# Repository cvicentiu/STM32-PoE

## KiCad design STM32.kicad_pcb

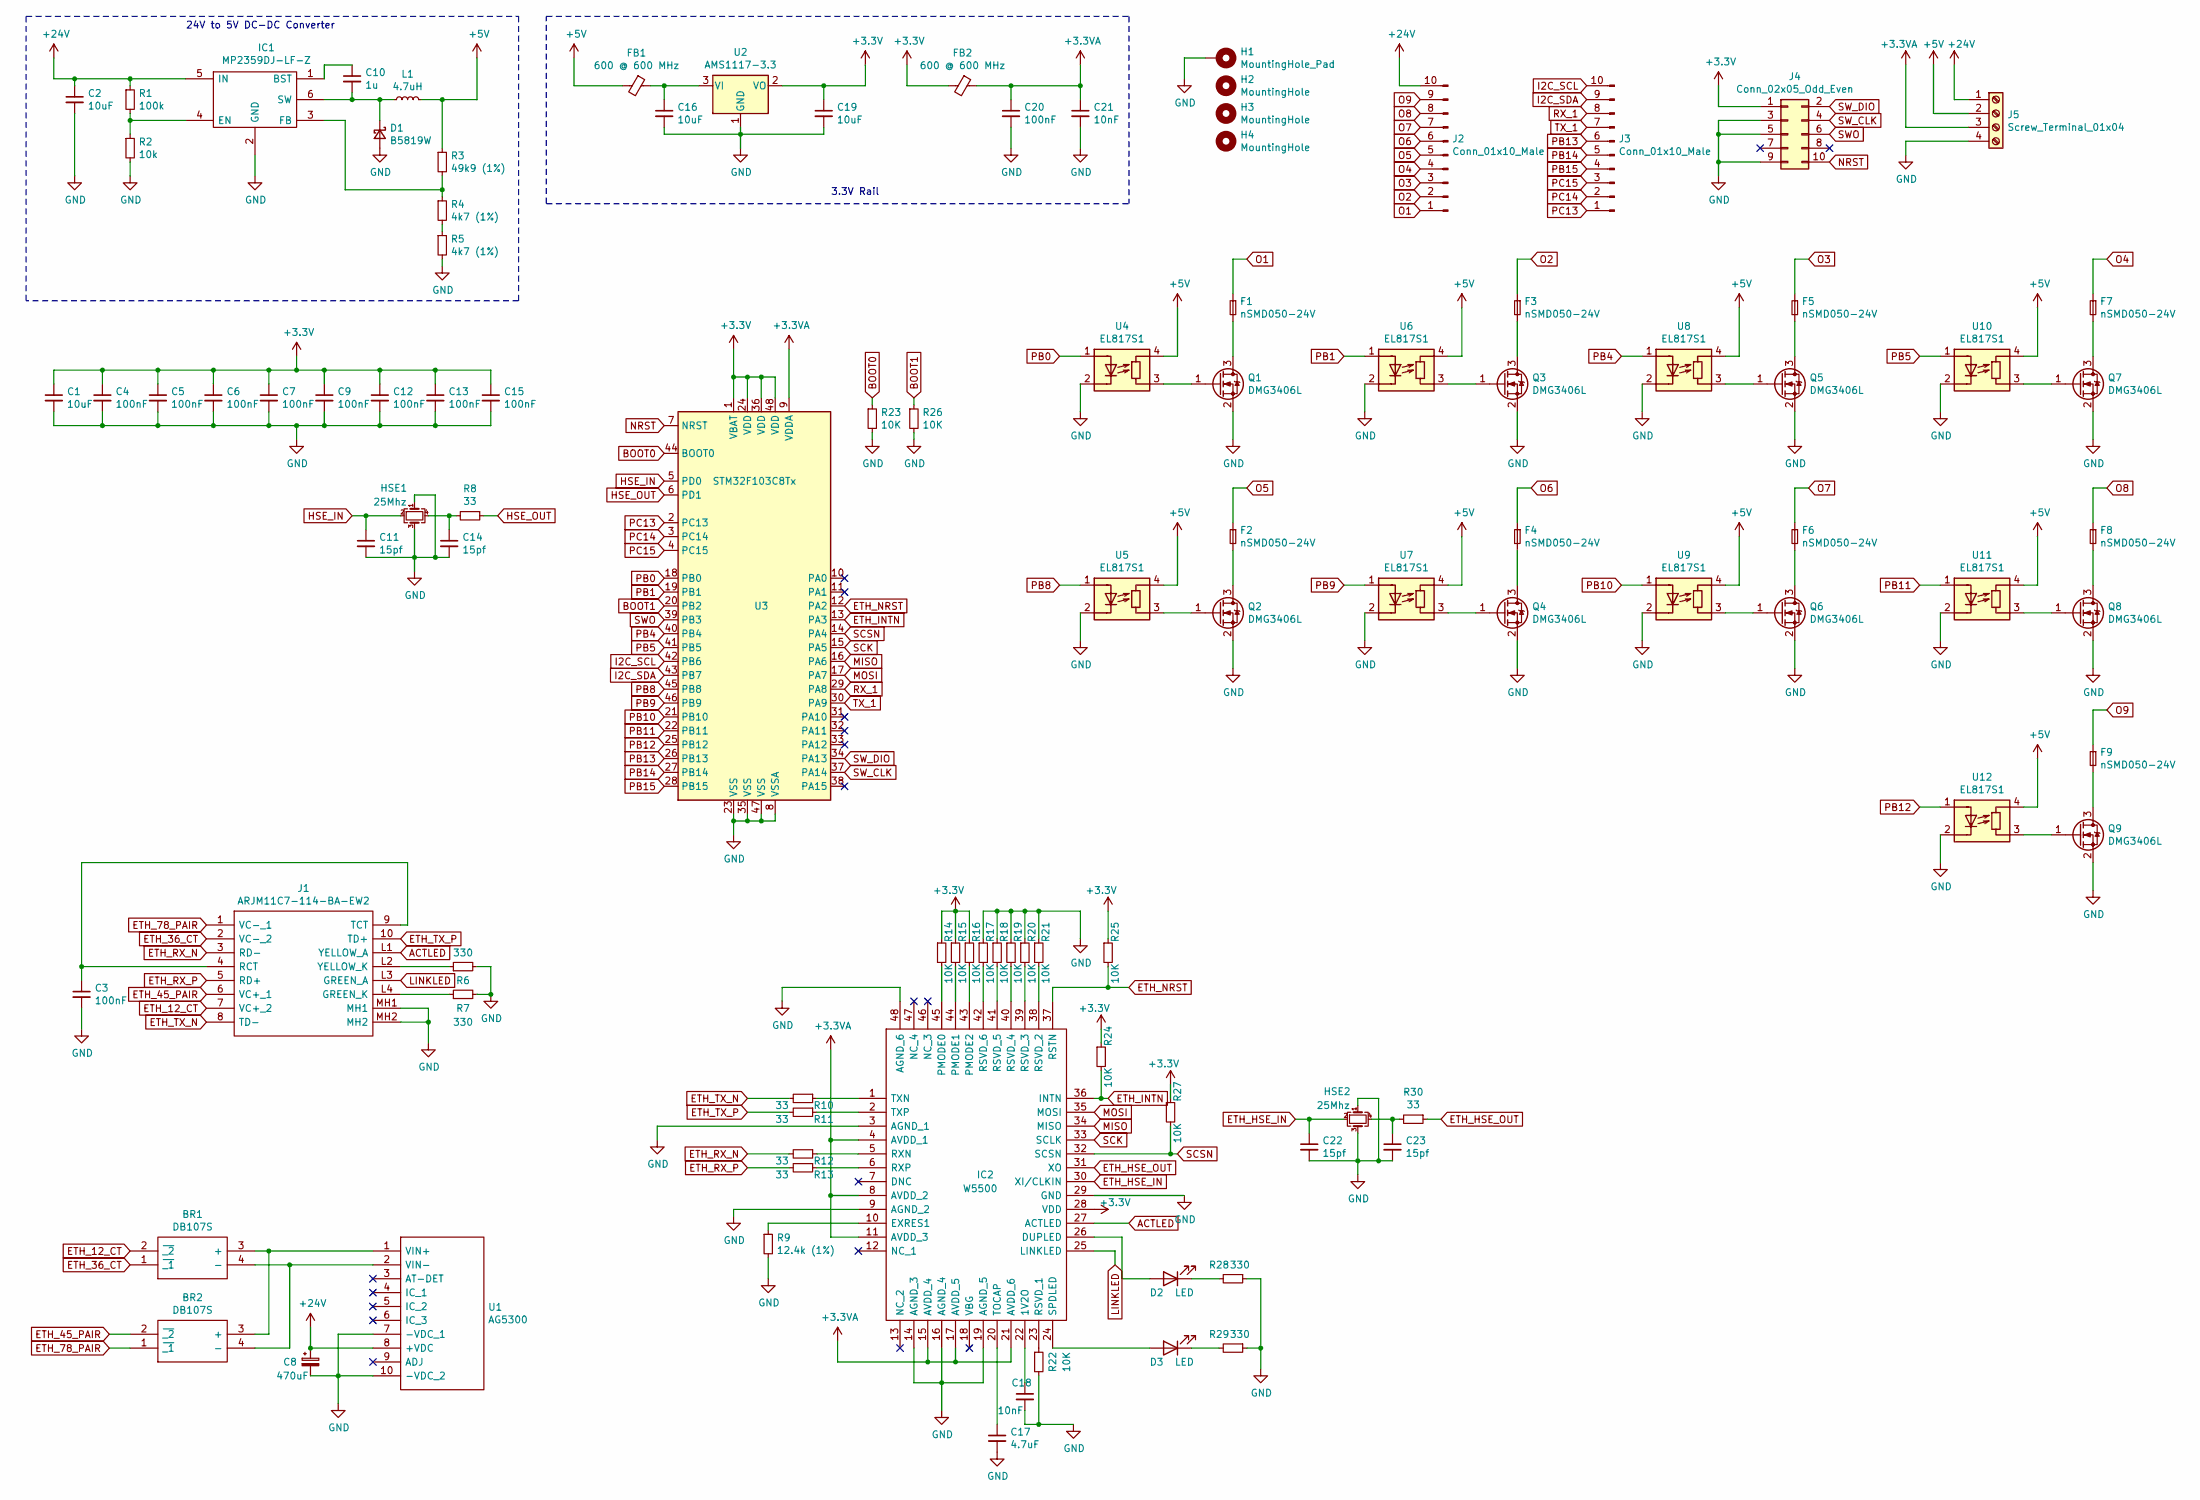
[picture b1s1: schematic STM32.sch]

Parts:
BR1, BR2: DB107S; SOP510P990X340-4N; Manufacturer_Part_Number DB107S; Mouser Part Number 583-DB107S
C1, C16, C19: 10uF; C_0402_1005Metric
C2: 10uF; C_0805_2012Metric
C3, C4, C5, C6, C7, C9, C12, C13, C15, C20: 100nF; C_0402_1005Metric
C8: 470uF; CP_Elec_10x10
C10: 1u; C_0805_2012Metric
C11, C14, C22, C23: 15pf; C_0402_1005Metric
C17: 4.7uF; C_0402_1005Metric
C18, C21: 10nF; C_0402_1005Metric
D1: B5819W; D_SOD-123
D2, D3: LED; LED_0805_2012Metric
F1, F2, F3, F4, F5, F6, F7, F8, F9: nSMD050-24V; Fuse_1206_3216Metric
FB1, FB2: 600 @ 600 MHz; L_0805_2012Metric
H1: MountingHole_Pad; MountingHole_3.2mm_M3_Pad_Via
H2, H3, H4: MountingHole; MountingHole_3.2mm_M3_Pad_Via
HSE1, HSE2: 25Mhz; Crystal_SMD_3225-4Pin_3.2x2.5mm
IC1: MP2359DJ-LF-Z; MP2359; Manufacturer_Part_Number MP2359DJ-LF-Z; Mouser Part Number 946-MP2359DJLFZ
IC2: W5500; QFP50P900X900X160-48N; Manufacturer_Part_Number W5500; Mouser Part Number 950-W5500
J1: ARJM11C7-114-BA-EW2; ARJM11C7114BAEW2; Manufacturer_Part_Number ARJM11C7-114-BA-EW2; Mouser Part Number 815-RJM11C7114BAEW2
J2, J3: Conn_01x10_Male; PinHeader_1x10_P2.54mm_Vertical
J4: Conn_02x05_Odd_Even; IDC-Header_2x05_P2.54mm_Vertical
J5: Screw_Terminal_01x04; TerminalBlock_Phoenix_MKDS-1,5-4_1x04_P5.00mm_Horizontal
L1: 4.7uH; L_1812_4532Metric
Q1, Q2, Q3, Q4, Q5, Q6, Q7, Q8, Q9: DMG3406L; SOT-23
R1: 100k; R_0805_2012Metric
R2: 10k; R_0805_2012Metric
R3: 49k9 (1%); R_0402_1005Metric
R4, R5: 4k7 (1%); R_0402_1005Metric
R6, R7, R28, R29: 330; R_0402_1005Metric
R8, R10, R11, R12, R13, R30: 33; R_0402_1005Metric
R9: 12.4k (1%); R_0402_1005Metric
R14, R15, R16, R17, R18, R19, R20, R21, R22, R23, R24, R25, R26, R27: 10K; R_0402_1005Metric
U1: AG5300; Manufacturer_Part_Number AG5300; Mouser Part Number 480-AG5300
U2: AMS1117-3.3; SOT-223-3_TabPin2
U3: STM32F103C8Tx; LQFP-48_7x7mm_P0.5mm
U4, U5, U6, U7, U8, U9, U10, U11, U12: EL817S1; SOP254P1030X390-4N

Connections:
+3.3VA: C20.1, C21.1, FB2.1, IC2.4 (AVDD_1), IC2.8 (AVDD_2), IC2.11 (AVDD_3), IC2.15 (AVDD_4), IC2.17 (AVDD_5), IC2.21 (AVDD_6), J5.3, U3.9 (VDDA)
+3V3: C1.1, C4.1, C5.1, C6.1, C7.1, C9.1, C12.1, C13.1, C15.1, C19.1, FB2.2, IC2.28 (VDD), J4.1, R14.1, R15.1, R16.1, R24.1, R25.1, R27.1, U2.2 (VO), U3.1 (VBAT), U3.24 (VDD), U3.36 (VDD), U3.48 (VDD)
+5V: FB1.2, J5.2, L1.2, R3.1, U4.4 (R), U5.4 (R), U6.4 (R), U7.4 (R), U8.4 (R), U9.4 (R), U10.4 (R), U11.4 (R), U12.4 (R)
+24V: C2.1, C8.1, IC1.5 (IN), J2.10, J5.1, R1.1, U1.8 (+VDC)
ACTLED: IC2.27 (ACTLED), J1.L1 (YELLOW_A)
BOOT0: R23.1, U3.44 (BOOT0)
BOOT1: R26.1, U3.20 (PB2)
ETH_12_CT: BR1.2 (~_2), J1.7 (VC+_2)
ETH_36_CT: BR1.1 (~_1), J1.2 (VC-_2)
ETH_45_PAIR: BR2.2 (~_2), J1.6 (VC+_1)
ETH_78_PAIR: BR2.1 (~_1), J1.1 (VC-_1)
ETH_HSE_IN: C22.1, HSE2.2, IC2.30 (XI/CLKIN)
ETH_HSE_OUT: IC2.31 (XO), R30.1
ETH_INTN: IC2.36 (INTN), R24.2, U3.13 (PA3)
ETH_NRST: IC2.37 (RSTN), R25.2, U3.12 (PA2)
ETH_RX_N: J1.3 (RD-), R12.2
ETH_RX_P: J1.5 (RD+), R13.2
ETH_TX_N: J1.8 (TD-), R10.2
ETH_TX_P: J1.10 (TD+), R11.2
GND: C1.2, C2.2, C3.2, C4.2, C5.2, C6.2, C7.2, C8.2, C9.2, C11.2, C12.2, C13.2, C14.2, C15.2, C16.2, C17.2, C18.2, C19.2, C20.2, C21.2, C22.2, C23.2, D1.2 (A), H1.1, HSE1.1, HSE1.3, HSE2.1, HSE2.3, IC1.2 (GND), IC2.3 (AGND_1), IC2.9 (AGND_2), IC2.14 (AGND_3), IC2.16 (AGND_4), IC2.19 (AGND_5), IC2.29 (GND), IC2.48 (AGND_6), J1.MH1, J1.MH2, J4.3, J4.5, J4.9, J5.4, Q1.2 (S), Q2.2 (S), Q3.2 (S), Q4.2 (S), Q5.2 (S), Q6.2 (S), Q7.2 (S), Q8.2 (S), Q9.2 (S), R2.2, R5.2, R6.2, R7.2, R9.2, R17.1, R18.1, R19.1, R20.1, R21.1, R22.2, R23.2, R26.2, R28.1, R29.1, U1.7 (-VDC_1), U1.10 (-VDC_2), U2.1 (GND), U3.8 (VSSA), U3.23 (VSS), U3.35 (VSS), U3.47 (VSS), U4.2 (K), U5.2 (K), U6.2 (K), U7.2 (K), U8.2 (K), U9.2 (K), U10.2 (K), U11.2 (K), U12.2 (K)
HSE_IN: C11.1, HSE1.2, U3.5 (PD0)
HSE_OUT: R8.1, U3.6 (PD1)
I2C_SCL: J3.10, U3.42 (PB6)
I2C_SDA: J3.9, U3.43 (PB7)
LINKLED: IC2.25 (LINKLED), J1.L3 (GREEN_A)
MISO: IC2.34 (MISO), U3.16 (PA6)
MOSI: IC2.35 (MOSI), U3.17 (PA7)
NRST: J4.10, U3.7 (NRST)
unnamed: BR1.3 (+), BR2.3 (+), U1.1 (VIN+)
unnamed: BR1.4 (-), BR2.4 (-), U1.2 (VIN-)
unnamed: C3.1, J1.4 (RCT), J1.9 (TCT)
unnamed: C10.1, IC1.1 (BST)
unnamed: C10.2, D1.1 (K), IC1.6 (SW), L1.1
unnamed: C14.1, HSE1.4, R8.2
unnamed: C16.1, FB1.1, U2.3 (VI)
unnamed: C17.1, IC2.20 (TOCAP)
unnamed: C18.1, IC2.22 (1V2O)
unnamed: C23.1, HSE2.4, R30.2
unnamed: D2.1 (K), R28.2
unnamed: D2.2 (A), IC2.26 (DUPLED)
unnamed: D3.1 (K), R29.2
unnamed: D3.2 (A), IC2.24 (SPDLED)
unnamed: F1.2, Q1.3 (D)
unnamed: F2.2, Q2.3 (D)
unnamed: F3.2, Q3.3 (D)
unnamed: F4.2, Q4.3 (D)
unnamed: F5.2, Q5.3 (D)
unnamed: F6.2, Q6.3 (D)
unnamed: F7.2, Q7.3 (D)
unnamed: F8.2, Q8.3 (D)
unnamed: F9.2, Q9.3 (D)
unnamed: IC1.3 (FB), R3.2, R4.1
unnamed: IC1.4 (EN), R1.2, R2.1
unnamed: IC2.1 (TXN), R10.1
unnamed: IC2.2 (TXP), R11.1
unnamed: IC2.5 (RXN), R12.1
unnamed: IC2.6 (RXP), R13.1
unnamed: IC2.10 (EXRES1), R9.1
unnamed: IC2.23 (RSVD_1), R22.1
unnamed: IC2.38 (RSVD_2), R21.2
unnamed: IC2.39 (RSVD_3), R20.2
unnamed: IC2.40 (RSVD_4), R19.2
unnamed: IC2.41 (RSVD_5), R18.2
unnamed: IC2.42 (RSVD_6), R17.2
unnamed: IC2.43 (PMODE2), R16.2
unnamed: IC2.44 (PMODE1), R15.2
unnamed: IC2.45 (PMODE0), R14.2
unnamed: J1.L2 (YELLOW_K), R6.1
unnamed: J1.L4 (GREEN_K), R7.1
unnamed: Q1.1 (G), U4.3 (R)
unnamed: Q2.1 (G), U5.3 (R)
unnamed: Q3.1 (G), U6.3 (R)
unnamed: Q4.1 (G), U7.3 (R)
unnamed: Q5.1 (G), U8.3 (R)
unnamed: Q6.1 (G), U9.3 (R)
unnamed: Q7.1 (G), U10.3 (R)
unnamed: Q8.1 (G), U11.3 (R)
unnamed: Q9.1 (G), U12.3 (R)
unnamed: R4.2, R5.1
O1: F1.1, J2.1
O2: F3.1, J2.2
O3: F5.1, J2.3
O4: F7.1, J2.4
O5: F2.1, J2.5
O6: F4.1, J2.6
O7: F6.1, J2.7
O8: F8.1, J2.8
O9: F9.1, J2.9
PB0: U3.18 (PB0), U4.1 (A)
PB1: U3.19 (PB1), U6.1 (A)
PB4: U3.40 (PB4), U8.1 (A)
PB5: U3.41 (PB5), U10.1 (A)
PB8: U3.45 (PB8), U5.1 (A)
PB9: U3.46 (PB9), U7.1 (A)
PB10: U3.21 (PB10), U9.1 (A)
PB11: U3.22 (PB11), U11.1 (A)
PB12: U3.25 (PB12), U12.1 (A)
PB13: J3.6, U3.26 (PB13)
PB14: J3.5, U3.27 (PB14)
PB15: J3.4, U3.28 (PB15)
PC13: J3.1, U3.2 (PC13)
PC14: J3.2, U3.3 (PC14)
PC15: J3.3, U3.4 (PC15)
RX_1: J3.8, U3.29 (PA8)
SCK: IC2.33 (SCLK), U3.15 (PA5)
SCSN: IC2.32 (SCSN), R27.2, U3.14 (PA4)
SWO: J4.6, U3.39 (PB3)
SW_CLK: J4.4, U3.37 (PA14)
SW_DIO: J4.2, U3.34 (PA13)
TX_1: J3.7, U3.30 (PA9)

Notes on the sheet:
24V to 5V DC-DC Converter
3.3V Rail

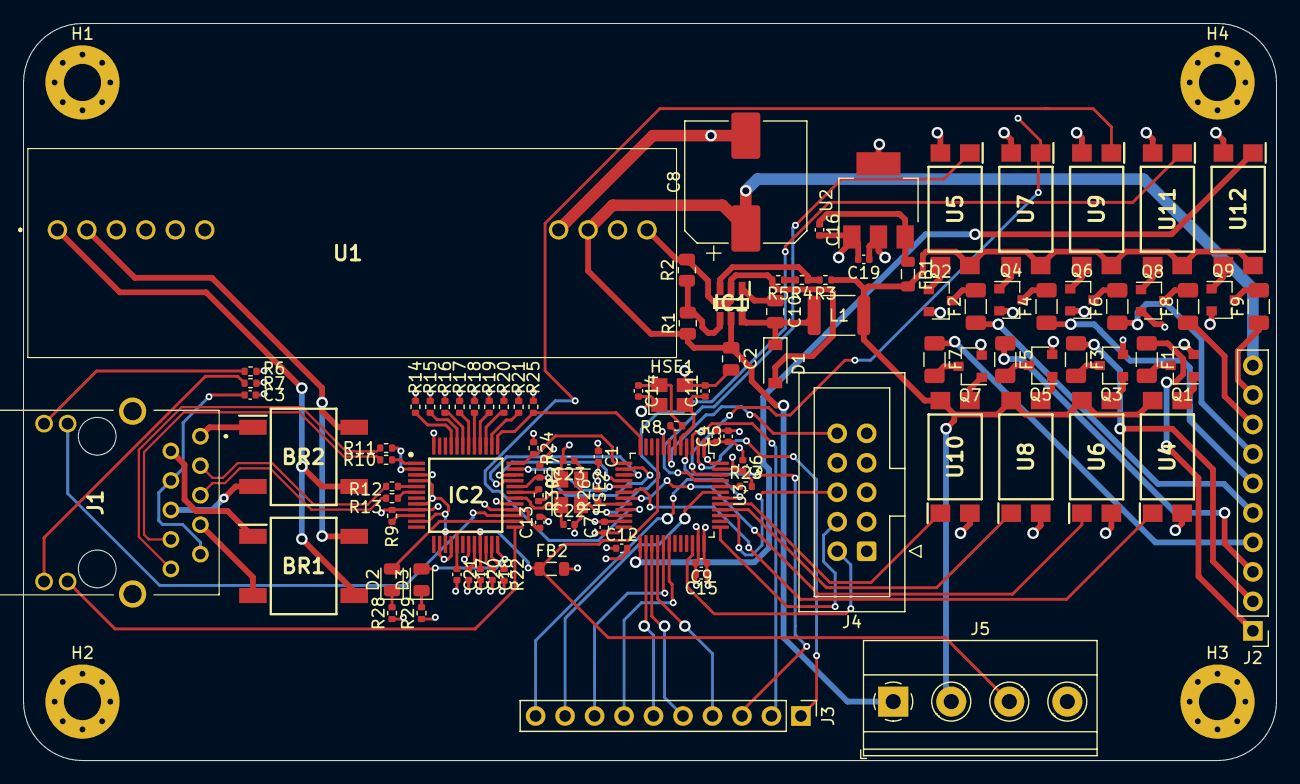
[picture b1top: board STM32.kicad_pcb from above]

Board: 4 copper layers, 108.0 x 63.5 mm, 104 parts (0 on the bottom side), 110 nets.

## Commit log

2020-10-17 Initial (dirty) commit
